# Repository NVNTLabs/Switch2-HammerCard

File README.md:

# NVNT's HammerCard Project

HammerCard is a non-game cartridge for the Nintendo Switch 2 which exposes the pins of the cartridge slot for (hopeful) sniffing/interception. Drawing from the historical use and design of "middle-man" cartridges (think: GameShark for N64) which allowed for code interception and manipulation, the HammerCard project utilizes a Nintendo Switch 2 cartridge slot soldered onto the PCB with a pin-header in-between.

The goal of this project is providing hardware that may be usable for the community in their efforts. A long-term and possible/hopeful outcome would be to create a Switch 1 / Switch 2 game cartridge reader/writer/dumper using findings from this.

---

## 📚 Table of Contents
- **Introduction**
  - [What Can I Do With This](#what-can-i-do-with-this)
  - [Goals](#goals)
  - [Status](#status)
  - [Warnings](#warnings)
- **Assets & Hardware Info**
    - [Nintendo Switch 2 Cartridge Slot Breakout Board](#nintendo-switch-2-cartridge-slot-breakout-board)
    - [HammerCard Proto](#hammercard-proto)
- [License](#license)

---

## What Can I Do With This?

Let's get the bad news out of the way. HammerCard, at least for now, isn't going to magically "unlock" things in your Nintendo Switch 2. However, the hope is that it can be used as a stepping stone or platform in furthering knowledge of the cartridge slot and game key encryptions in place.

---
## Goals

- ✅ Upload Version 0.1 "Switch 2 Cartridge Breakout Sniffer Mk2" - Without Nintendo Switch 2 Card Slot (DONE)
- ✅ Upload Version 0.2 "Switch 2 Hammer Card Mk1" Proto - With Nintendo Switch 2 Card Slot (DONE)
- 🔲 Fix Switch 2 Card/Cartridge Slot Pinout & Footprint
- 🔲 Make proper 3D enclosure, and re-work PCB to be smaller and better looking
- 🔲 TBD
---

## Status

Very early work in progress. In the file there is both the old version "Cartridge Breakout Sniffer Mk2" and the prototype of HammerCard. The prototype has some alignment issues for the Cart Slot pins, and I'm currently improving these.

---

## Warnings

- Use at your own risk. We are **not liable** for any damage to your Switch 2, game cards or other things.
  
---

## Bill of Materials (BOM)

| Reference | Quantity | Description                             | Part Number        | Manufacturer   |
|-----------|----------|-----------------------------------------|--------------------|----------------|
|J3         | 1        | Nintendo Switch 2 Cartridge Slot        |*                   | On AliExpress  |
|J1         | 1        | 1x17 Pin Header                         | N/A                | *              |

---

### Nintendo Switch 2 Cartridge Slot Breakout Board

This is what started it all. A curiosity of sorts. A breakout cartridge for the Nintendo Switch 2 which breaks out the cartridge slot pins for probing.

---

### HammerCard Proto

A very WIP, ugly, gumstick PCB prototype has been uploaded. The footprint/pinout of the Switch 2 game card slot isn't finalized and needs to be improved.

---
## License

This hardware design is licensed under the **CERN Open Hardware License Version 2 – Strongly Reciprocal (CERN-OHL-S v2)**.

The software/firmware design is licensed under the **GNU General Public License v3.0 (GPLv3)**

The documentation and readme is licensed under the **Creative Commons Attribution-ShareAlike 4.0 International (CC-BY-SA 4.0)**.

See [LICENSE](LICENSE.txt), [LICENSE-HARDWARE](LICENSE-HARDWARE.txt) and [LICENSE-DOCUMENTATION](LICENSE-DOCUMENTATION.txt) for more information.

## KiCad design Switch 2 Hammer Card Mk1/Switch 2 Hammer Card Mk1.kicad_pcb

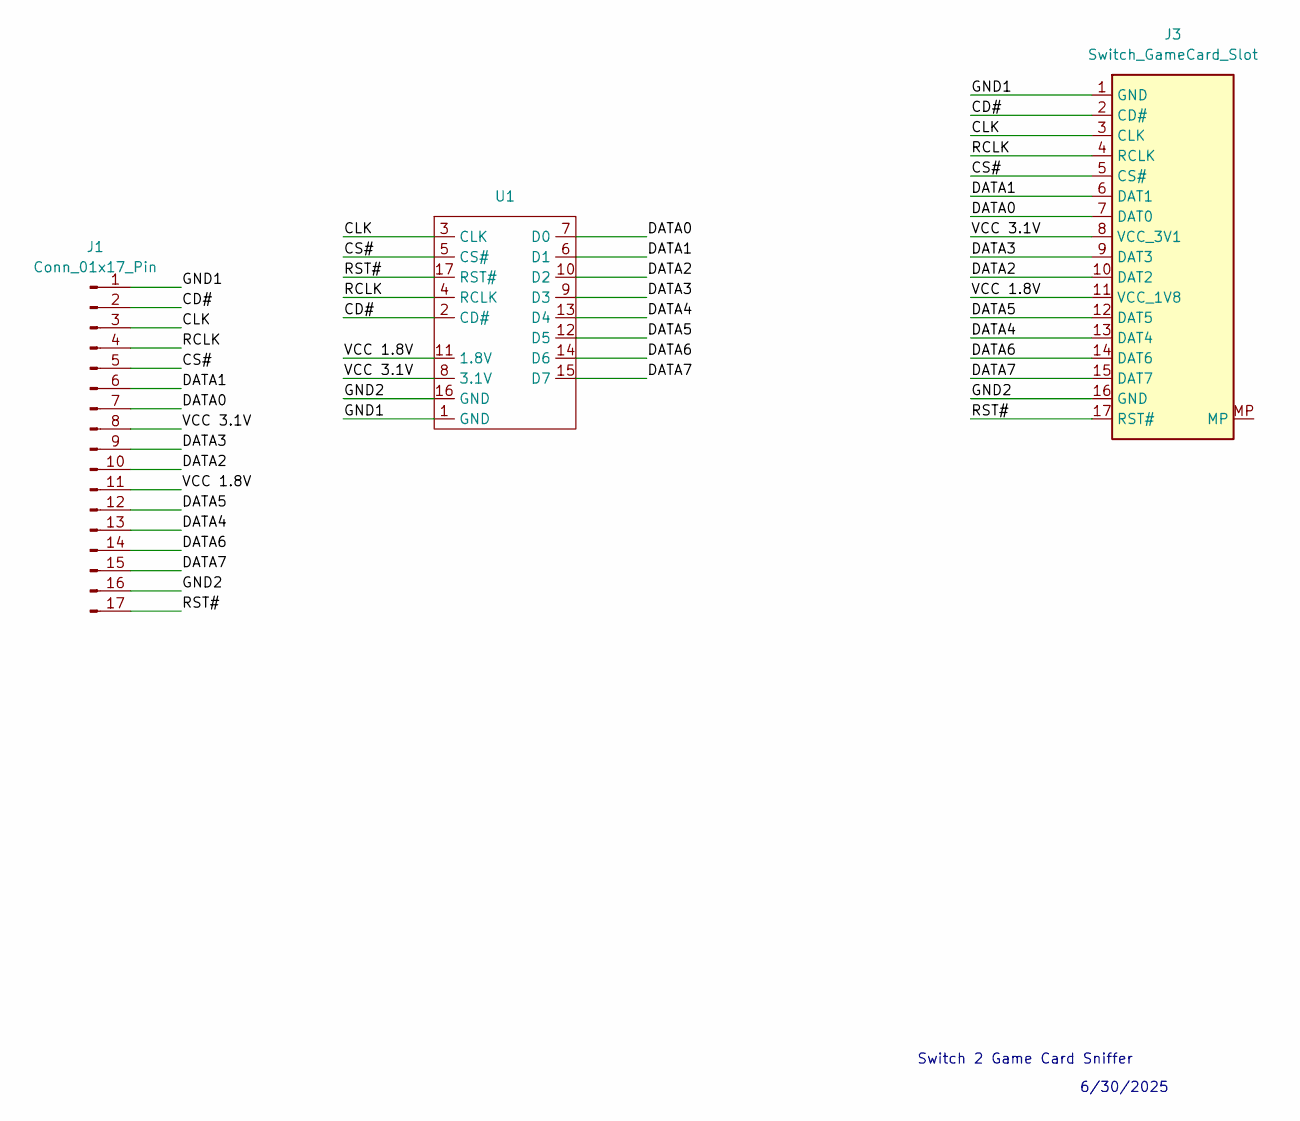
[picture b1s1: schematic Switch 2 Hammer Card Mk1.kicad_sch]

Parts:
J1: Conn_01x17_Pin; PinHeader_1x17_P2.54mm_Vertical
J3: Switch_GameCard_Slot; Nintendo_Switch_GameCard_Slot_1x17_P1.00mm
U1: Gamecard

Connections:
/CD#: J1.2, J3.2 (CD#), U1.2 (CD#)
/CLK: J1.3, J3.3 (CLK), U1.3 (CLK)
/CS#: J1.5, J3.5 (CS#), U1.5 (CS#)
/DATA0: J1.7, J3.7 (DAT0), U1.7 (D0)
/DATA1: J1.6, J3.6 (DAT1), U1.6 (D1)
/DATA2: J1.10, J3.10 (DAT2), U1.10 (D2)
/DATA3: J1.9, J3.9 (DAT3), U1.9 (D3)
/DATA4: J1.13, J3.13 (DAT4), U1.13 (D4)
/DATA5: J1.12, J3.12 (DAT5), U1.12 (D5)
/DATA6: J1.14, J3.14 (DAT6), U1.14 (D6)
/DATA7: J1.15, J3.15 (DAT7), U1.15 (D7)
/GND1: J1.1, J3.1 (GND), U1.1 (GND)
/GND2: J1.16, J3.16 (GND), U1.16 (GND)
/RCLK: J1.4, J3.4 (RCLK), U1.4 (RCLK)
/RST#: J1.17, J3.17 (RST#), U1.17 (RST#)
/VCC 1.8V: J1.11, J3.11 (VCC_1V8), U1.11 (1.8V)
/VCC 3.1V: J1.8, J3.8 (VCC_3V1), U1.8 (3.1V)

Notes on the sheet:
6/30/2025
Switch 2 Game Card Sniffer

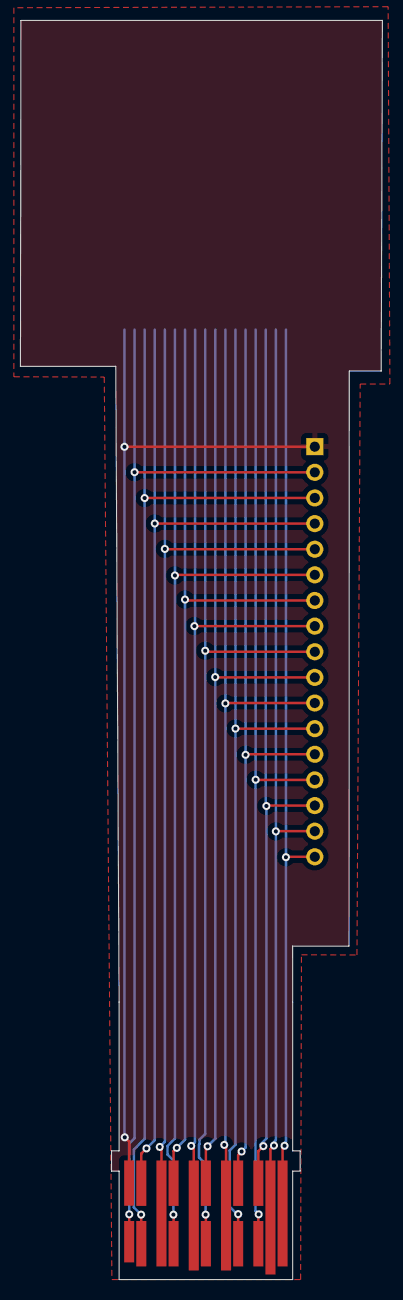
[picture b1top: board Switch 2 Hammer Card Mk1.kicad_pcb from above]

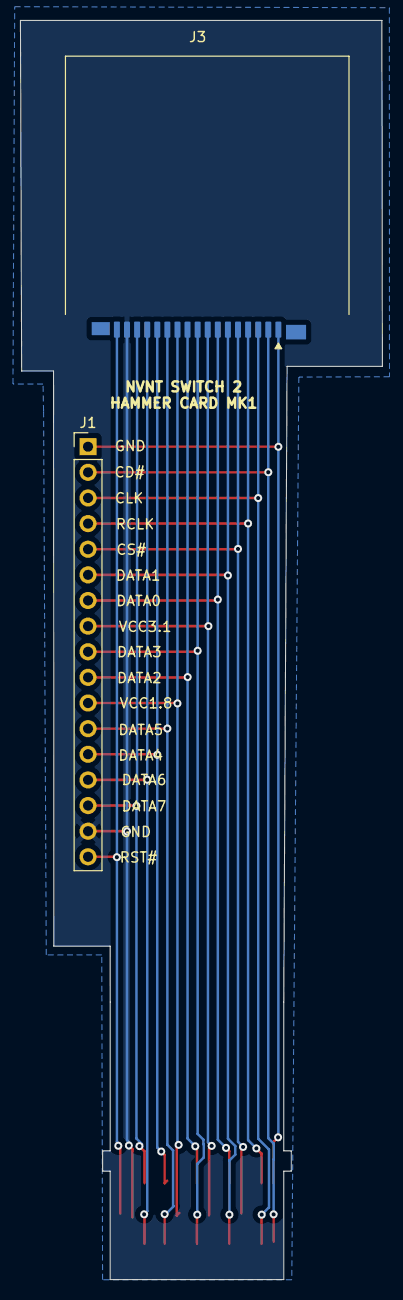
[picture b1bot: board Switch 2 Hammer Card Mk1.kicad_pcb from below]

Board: 2 copper layers, 35.9 x 124.8 mm, 3 parts (2 on the bottom side), 17 nets.
